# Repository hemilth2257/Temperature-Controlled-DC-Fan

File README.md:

# Temperature-Controlled-DC-Fan
Temperature Controlled DC fan built with an Arduino Nano, LM358 op-amp, and a custom KiCad PC

An automated cooling system built with an Arduino Nano, an LM358 op-amp, and an NTC thermistor. This project was developed during my 2nd semester of BTech in Electronics Engineering.

# Overview
This hardware project bridges analog sensing and digital control. An NTC thermistor tracks the ambient temperature, and an LM358 op-amp acts as an open-loop comparator to trigger the cooling fan when the temperature exceeds a precise 40°C threshold. The Arduino Nano processes the ADC readings and multiplexes two 7-segment displays at 200 Hz for a flicker-free real-time temperature readout. 

The system progressed from a dense breadboard prototype to a fully routed custom PCB designed in KiCad.

## Hardware Components
* **Microcontroller:** Arduino Nano (ATmega328P)
* **Temperature Sensor:** 10k NTC Thermistor
* **Analog Comparator:** LM358 Dual Op-Amp
* **Power Switching:** BD139 NPN Transistor (with 1N4007 flyback diode)
* **Display:** 2x Common Cathode 7-Segment Displays
* **Output:** 12V DC Fan

##  Features
* **Custom PCB:** Designed in KiCad with strict 45-degree track routing and zero DRC errors.
* **Firmware Optimization:** Custom C++ code to calculate temperature via the Steinhart-Hart equation and handle 200 Hz display multiplexing to eliminate ghosting.
* **Hardware Protection:** Integrated flyback diode to suppress back-EMF spikes from the fan motor.

##  Project Files
* `dc_fan_controller.ino`: The main Arduino C++ source code.
* `microproject_sem2_fixed.pdf`: Full engineering project report, including circuit analysis, KiCad schematics, and testing methodologies.

## 📸 Circuit & PCB Design

Here is the complete circuit schematic designed in KiCad:

Here is the 3D render of the final routed board:

And here is the 2D copper track layout showing the strict 45-degree routing:

##  Author
**Hemil Thakkar & Het Dave** Electronics Engineering Students at BVM Engineering College.

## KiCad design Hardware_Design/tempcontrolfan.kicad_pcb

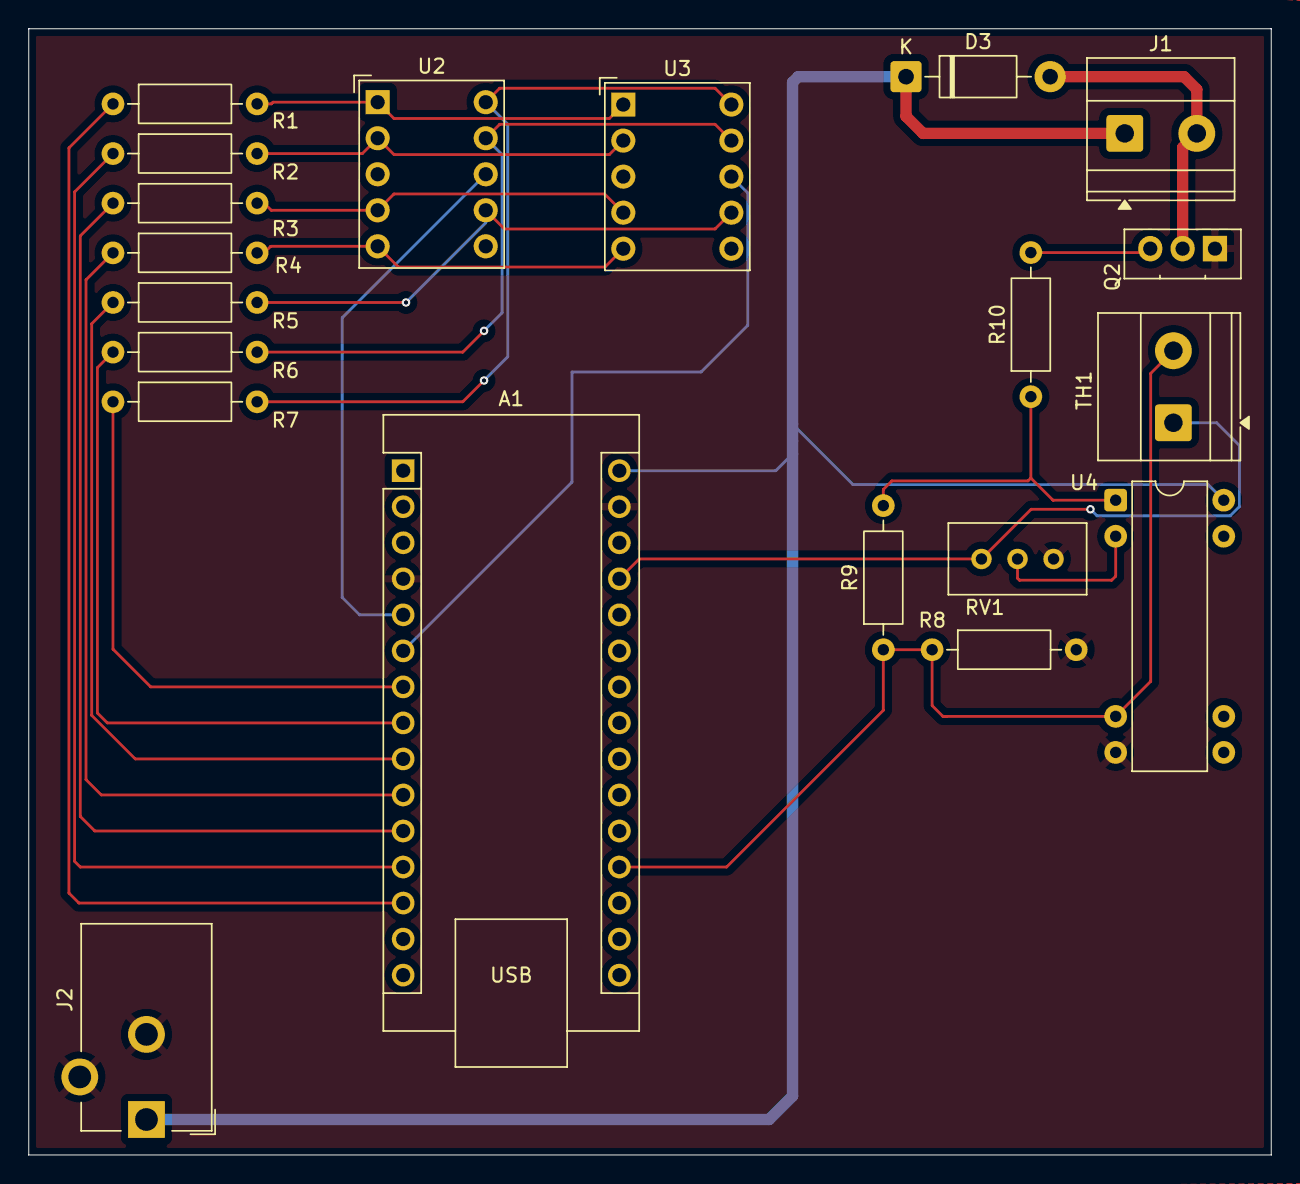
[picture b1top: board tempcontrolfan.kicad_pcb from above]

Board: 2 copper layers, 87.6 x 79.4 mm, 20 parts (0 on the bottom side), 24 nets.

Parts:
A1: Arduino_Nano_v2.x; Arduino_Nano
D3: 1N4007; D_DO-41_SOD81_P10.16mm_Horizontal
J1: Screw_Terminal_01x02; TerminalBlock_Phoenix_MKDS-1,5-2-5.08_1x02_P5.08mm_Horizont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
J2: Barrel_Jack_Switch; BarrelJack_CUI_PJ-102AH_Horizontal
Q2: BD139; TO-126-3_Vertical
R1, R2, R3, R4, R5, R6, R7: 330; R_Axial_DIN0207_L6.3mm_D2.5mm_P10.16mm_Horizontal
R8: 10k; R_Axial_DIN0207_L6.3mm_D2.5mm_P10.16mm_Horizontal
R9: 100k; R_Axial_DIN0207_L6.3mm_D2.5mm_P10.16mm_Horizontal
R10: 1k; R_Axial_DIN0207_L6.3mm_D2.5mm_P10.16mm_Horizontal
RV1: 10k; Potentiometer_Bourns_3296W_Vertical
TH1: Thermistor_NTC; TerminalBlock_Phoenix_MKDS-1,5-2-5.08_1x02_P5.08mm_Horizont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
U2, U3: SC39-11EWA; Sx39-1xxxxx
U4: LM358; DIP-8-16_W7.62mm

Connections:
+5V: A1.27 (+5V), RV1.1, TH1.1
+12V: A1.30 (VIN), D3.1 (K), J1.1, J2.1, U4.8 (V+)
/TEMP_SENSE: A1.19 (A0), R8.1, R9.1, TH1.2, U4.3 (+)
GND: A1.4 (GND), A1.29 (GND), J2.2, J2.3, Q2.1 (E), R8.2, RV1.3, U4.4 (V-)
unnamed: A1.5 (D2), U2.8 (CC)
unnamed: A1.6 (D3), U3.8 (CC)
unnamed: A1.7 (D4), R7.1
unnamed: A1.8 (D5), R6.1
unnamed: A1.9 (D6), R5.1
unnamed: A1.10 (D7), R4.1
unnamed: A1.11 (D8), R3.1
unnamed: A1.12 (D9), R2.1
unnamed: A1.13 (D10), R1.1
unnamed: D3.2 (A), J1.2, Q2.2 (C)
unnamed: Q2.3 (B), R10.2
unnamed: R9.2, R10.1, U4.1
unnamed: R7.2, U2.10 (A), U3.10 (A)
unnamed: R6.2, U2.9 (B), U3.9 (B)
unnamed: R5.2, U2.7 (C), U3.7 (C)
unnamed: R4.2, U2.5 (D), U3.5 (D)
unnamed: R3.2, U2.4 (E), U3.4 (E)
unnamed: R2.2, U2.2 (F), U3.2 (F)
unnamed: R1.2, U2.1 (G), U3.1 (G)
unnamed: RV1.2, U4.2 (-)

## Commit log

2026-05-29 Add DC fan controller code with temperature display
    Includes NTC thermistor analog reading logic and the 200Hz multiplexing setup for the dual 7segment displays to prevent ghosting
2026-05-29 Enhance README with project details and author info
    Expanded project description and added detailed sections on hardware components, features, project files, and author information.
2026-05-29 Enhance README with circuit and PCB design visuals
    Added circuit schematic and PCB design images to README.
2026-05-29 Fix image paths in README.md
    Corrected image paths in README for consistency.
2026-05-29 Fix image paths in README.md
2026-05-29 Rename pcb 3d.PNG to pcb_3d.PNG
2026-05-29 Correct 3D PCB render image filename
    Fixed image filename for 3D PCB render in README.
